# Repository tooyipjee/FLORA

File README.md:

FLORA: The Smart Garden Weather Station and Soil Moisture Monitor

In 2022, Europe faced its worst drought in over four decades. This marked a significant turning point for sustainable gardening practices across the continent. Amidst this crisis, there is an emerging solution that empowers communities to be more resilient and adaptive to extreme climates: FLORA - A Smart Garden Weather Station with Soil Moisture Monitoring.

The Need for Water-Efficient Practices in Europe's Gardens, Allotments, and Small Farms

The current climate crisis has made it imperative to rethink our approach towards water management and conservation. With the recent drought conditions across Europe, there is an urgent need to implement sustainable practices that can ensure a reliable food supply while conserving precious resources. The project at hand seeks to address this by creating smarter gardens and farms that are efficient in their use of water, thereby mitigating the risks associated with climate change-induced adversities.

Introducing FLORA: A Proof of Concept for Sustainable Gardening

FLORA is an innovative prototyping platform designed to enhance garden and farm productivity while promoting water conservation and sustainability. Built around a low-cost ESP32 SoC, it supports WiFi, BLE, and LoRa connectivity for efficient communication with other smart devices on the same network frequency band up to 3 km away.
e

The platform includes an ambient sensor and various inputs for integrating soil moisture sensors, providing a comprehensive view of environmental factors that influence plant growth. The goal is not just about making gardens more efficient; it's also about bringing communities back in control of their food production systems by making gardening processes rewarding and as effortless as possible.

What Makes FLORA Unique?

Long Range Communication: With the LoRa module, FLORA offers long-range communication up to approximately 2 miles/3 km. This feature is particularly beneficial for expansive gardens or allotments that require monitoring over larger areas without compromising on connectivity.

Soil Moisture Sensor Integration: The companion soil moisture sensor, based on capacitive sensing technology and insulated to prevent corrosion, provides real-time data about the water content in the top layer of the soil. This information is essential for optimizing irrigation practices and avoiding unnecessary water wastage.

Solar Power: FLORA runs on a solar panel powered by coin cell batteries, ensuring it operates sustainably without relying on conventional energy sources.

Vinduino Project Inspiration

The inspiration behind the design of FLORA comes from Reinier van der Lee's project, Vinduino, which showcases how simple electronics sensors can significantly reduce water usage in agriculture by up to 25%. The underlying principles and technologies have been adapted for use in gardening applications.

Building on Plant-Bot Project Experience

Reinier's experience with the Plant-Bot project laid a solid foundation for designing FLORA, allowing it to evolve into an outdoor-focused system that caters specifically to multiple plants and gardens.

Key Features of FLORA:

Compatibility with WiFi, BLE, and LoRa connectivity for seamless communication

Temperature accuracy within 0.3°C and humidity accuracy up to 3% RH using the SHT20 sensor

Capable of integrating various soil moisture sensors with capacitive-based technology

Long-range communication capabilities, extending FLORA's coverage area significantly

Efficient energy consumption powered by a solar panel and coin cell battery system

User-friendly design that empowers gardeners to take control of their plant care processes

Versatility in customization and integration with other smart devices within the same network frequency band

Specification Details:

Microcontroller: ESP32-WROOM-32E

WiFi Support: 802.11b/g/n standard

Bluetooth Capabilities: BLE 4.2 version

Flash Memory: 8MB capacity for firmware storage and execution

Programming Interface: USB over UART (CP2102) for direct programming and control

Environment Sensor: Incorporates the SHT20 sensor to measure temperature and humidity accurately

Soil Moisture Measurement: Utilizes capacitive sensing technology for reliable soil moisture readings

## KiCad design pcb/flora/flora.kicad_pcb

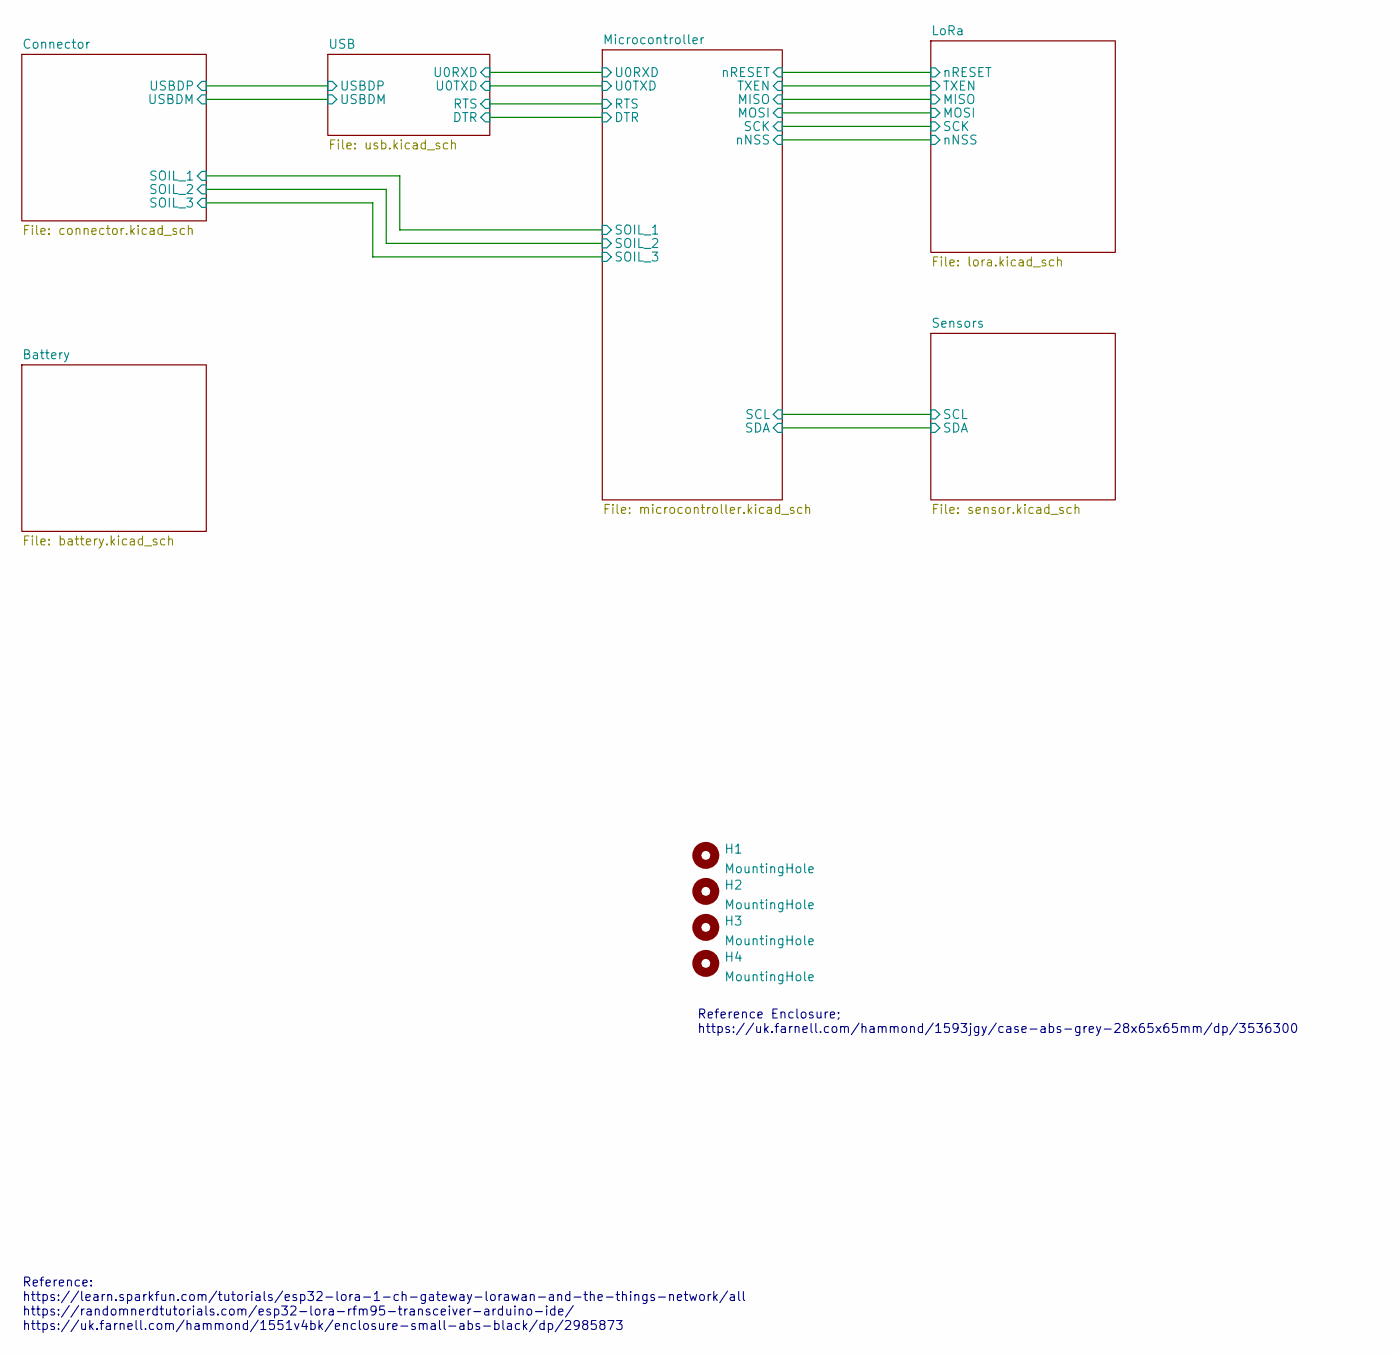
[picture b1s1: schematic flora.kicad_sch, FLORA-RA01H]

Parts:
H1, H2, H3, H4: MountingHole; MountingHole_3.2mm_M3_Small

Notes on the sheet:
Reference Enclosure; https://uk.farnell.com/hammond/1593jgy/case-abs-grey-28x65x65mm/dp/3536300
Reference: https://learn.sparkfun.com/tutorials/esp32-lora-1-ch-gateway-lorawan-and-the-things-network/all https://randomnerdtutorials.com/esp32-lora-rfm95-transceiver-arduino-ide/ https://uk.farnell.com/hammond/1551v4bk/enclosure-small-abs-black/dp/2985873

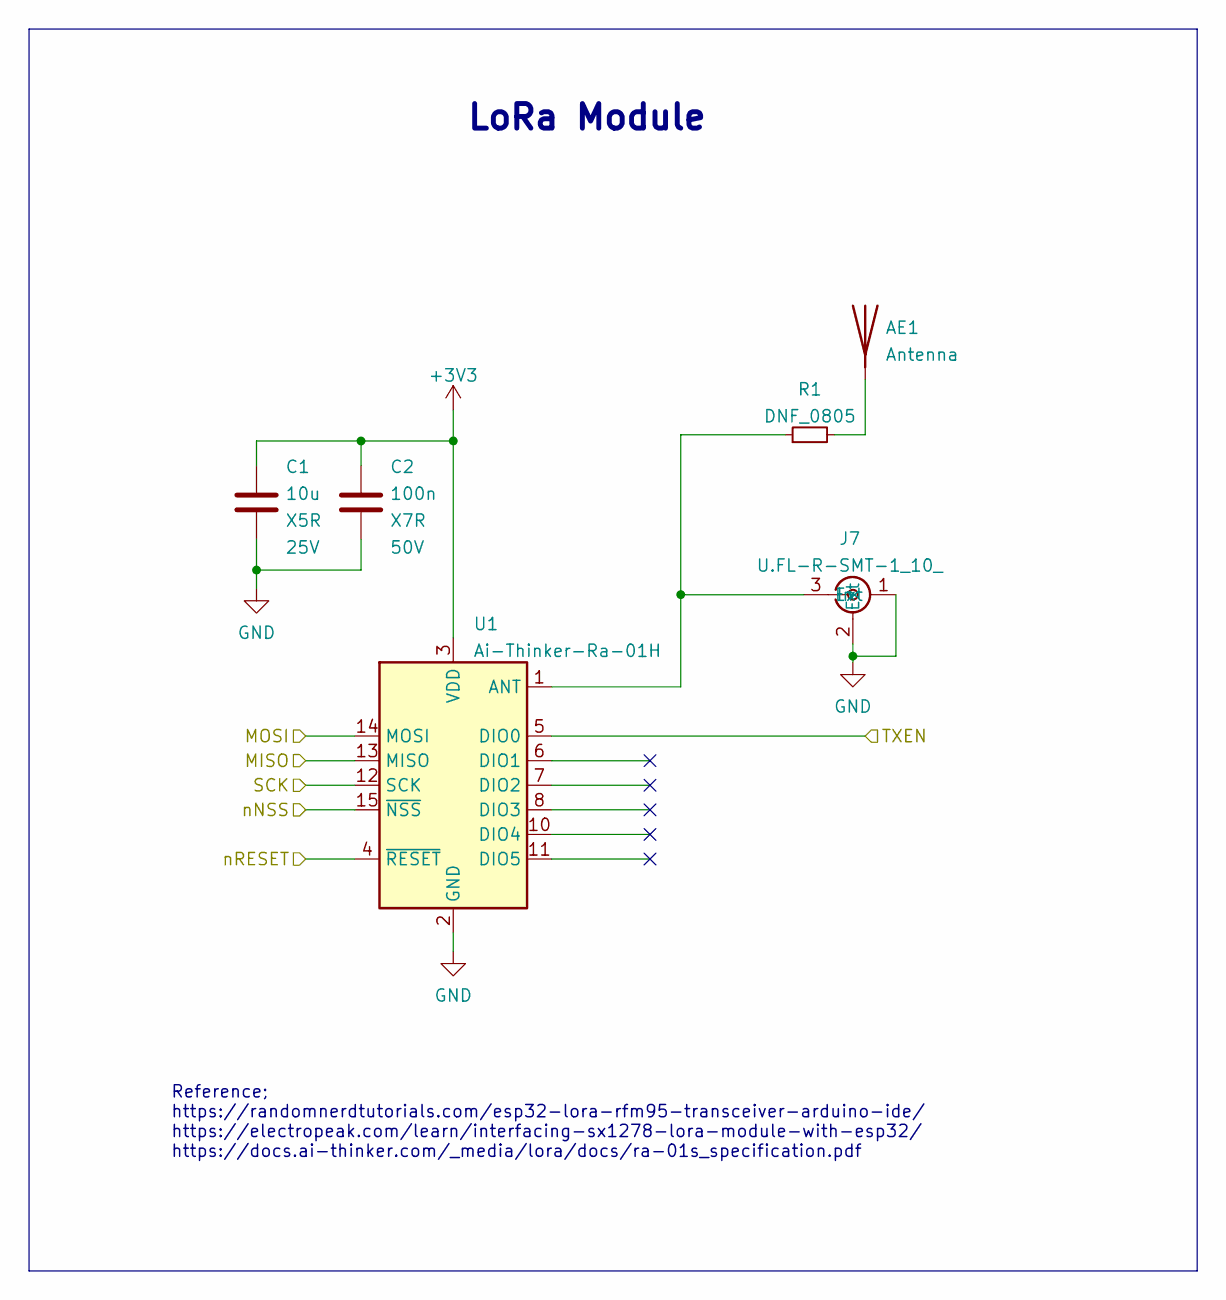
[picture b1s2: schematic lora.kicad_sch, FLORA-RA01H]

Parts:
AE1: Antenna; Texas_SWRA416_868MHz_915MHz
C1: 10u; C_0805_2012Metric; Voltage 25V; LCSC C15850
C2: 100n; C_0402_1005Metric; Voltage 50V; LCSC C307331
J7: U.FL-R-SMT-1_10_; Manufacturer_Part_Number U.FL-R-SMT-1(10); Mouser Part Number 798-U.FL-R-SMT-110
R1: DNF_0805; R_0805_2012Metric_Pad1.20x1.40mm_HandSolder
U1: Ai-Thinker-Ra-01H; Ai-Thinker-Ra-01-LoRa; LCSC C503593

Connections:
+3V3: C1.1, C2.1, U1.3 (VDD); also elsewhere on the board
GND: C1.2, C2.2, J7.1 (Ext), J7.2 (Ext), U1.2 (GND), U1.9 (GND), U1.16 (GND); also elsewhere on the board
GPIO2: U1.5 (DIO0); also elsewhere on the board
GPIO5: U1.15 (~NSS); also elsewhere on the board
GPIO14: U1.4 (~RESET); also elsewhere on the board
GPIO18: U1.12 (SCK); also elsewhere on the board
GPIO19: U1.13 (MISO); also elsewhere on the board
GPIO23: U1.14 (MOSI); also elsewhere on the board
unnamed: AE1.1 (A), R1.2
unnamed: J7.3 (In), R1.1, U1.1 (ANT)

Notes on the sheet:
LoRa Module
Reference; https://randomnerdtutorials.com/esp32-lora-rfm95-transceiver-arduino-ide/ https://electropeak.com/learn/interfacing-sx1278-lora-module-with-esp32/ https://docs.ai-thinker.com/_media/lora/docs/ra-01s_specification.pdf

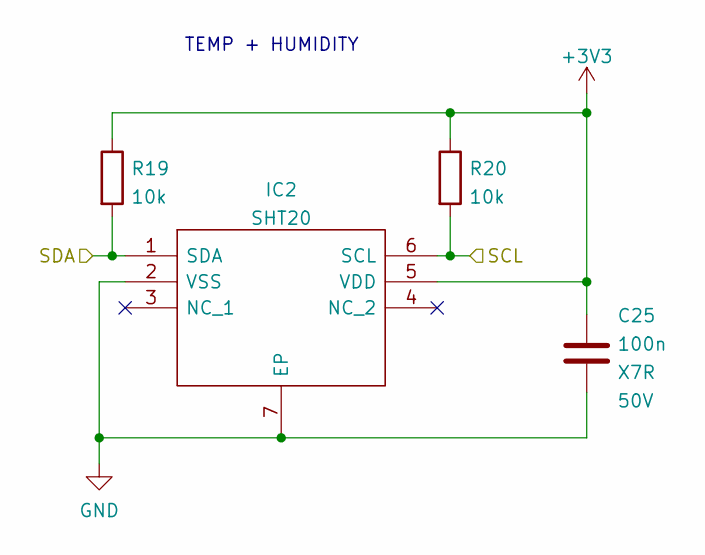
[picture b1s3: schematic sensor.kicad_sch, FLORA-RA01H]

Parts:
C25: 100n; C_0402_1005Metric; Voltage 50V; LCSC C307331
IC2: SHT20; SON100P300X300X110-7N; Mouser Part Number 403-SHT20
R19, R20: 10k; R_0402_1005Metric; LCSC C25744

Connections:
+3V3: C25.1, IC2.5 (VDD), R19.1, R20.1; also elsewhere on the board
GND: C25.2, IC2.2 (VSS), IC2.7 (EP); also elsewhere on the board
GPIO16: IC2.1 (SDA), R19.2; also elsewhere on the board
GPIO17: IC2.6 (SCL), R20.2; also elsewhere on the board

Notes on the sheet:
TEMP + HUMIDITY

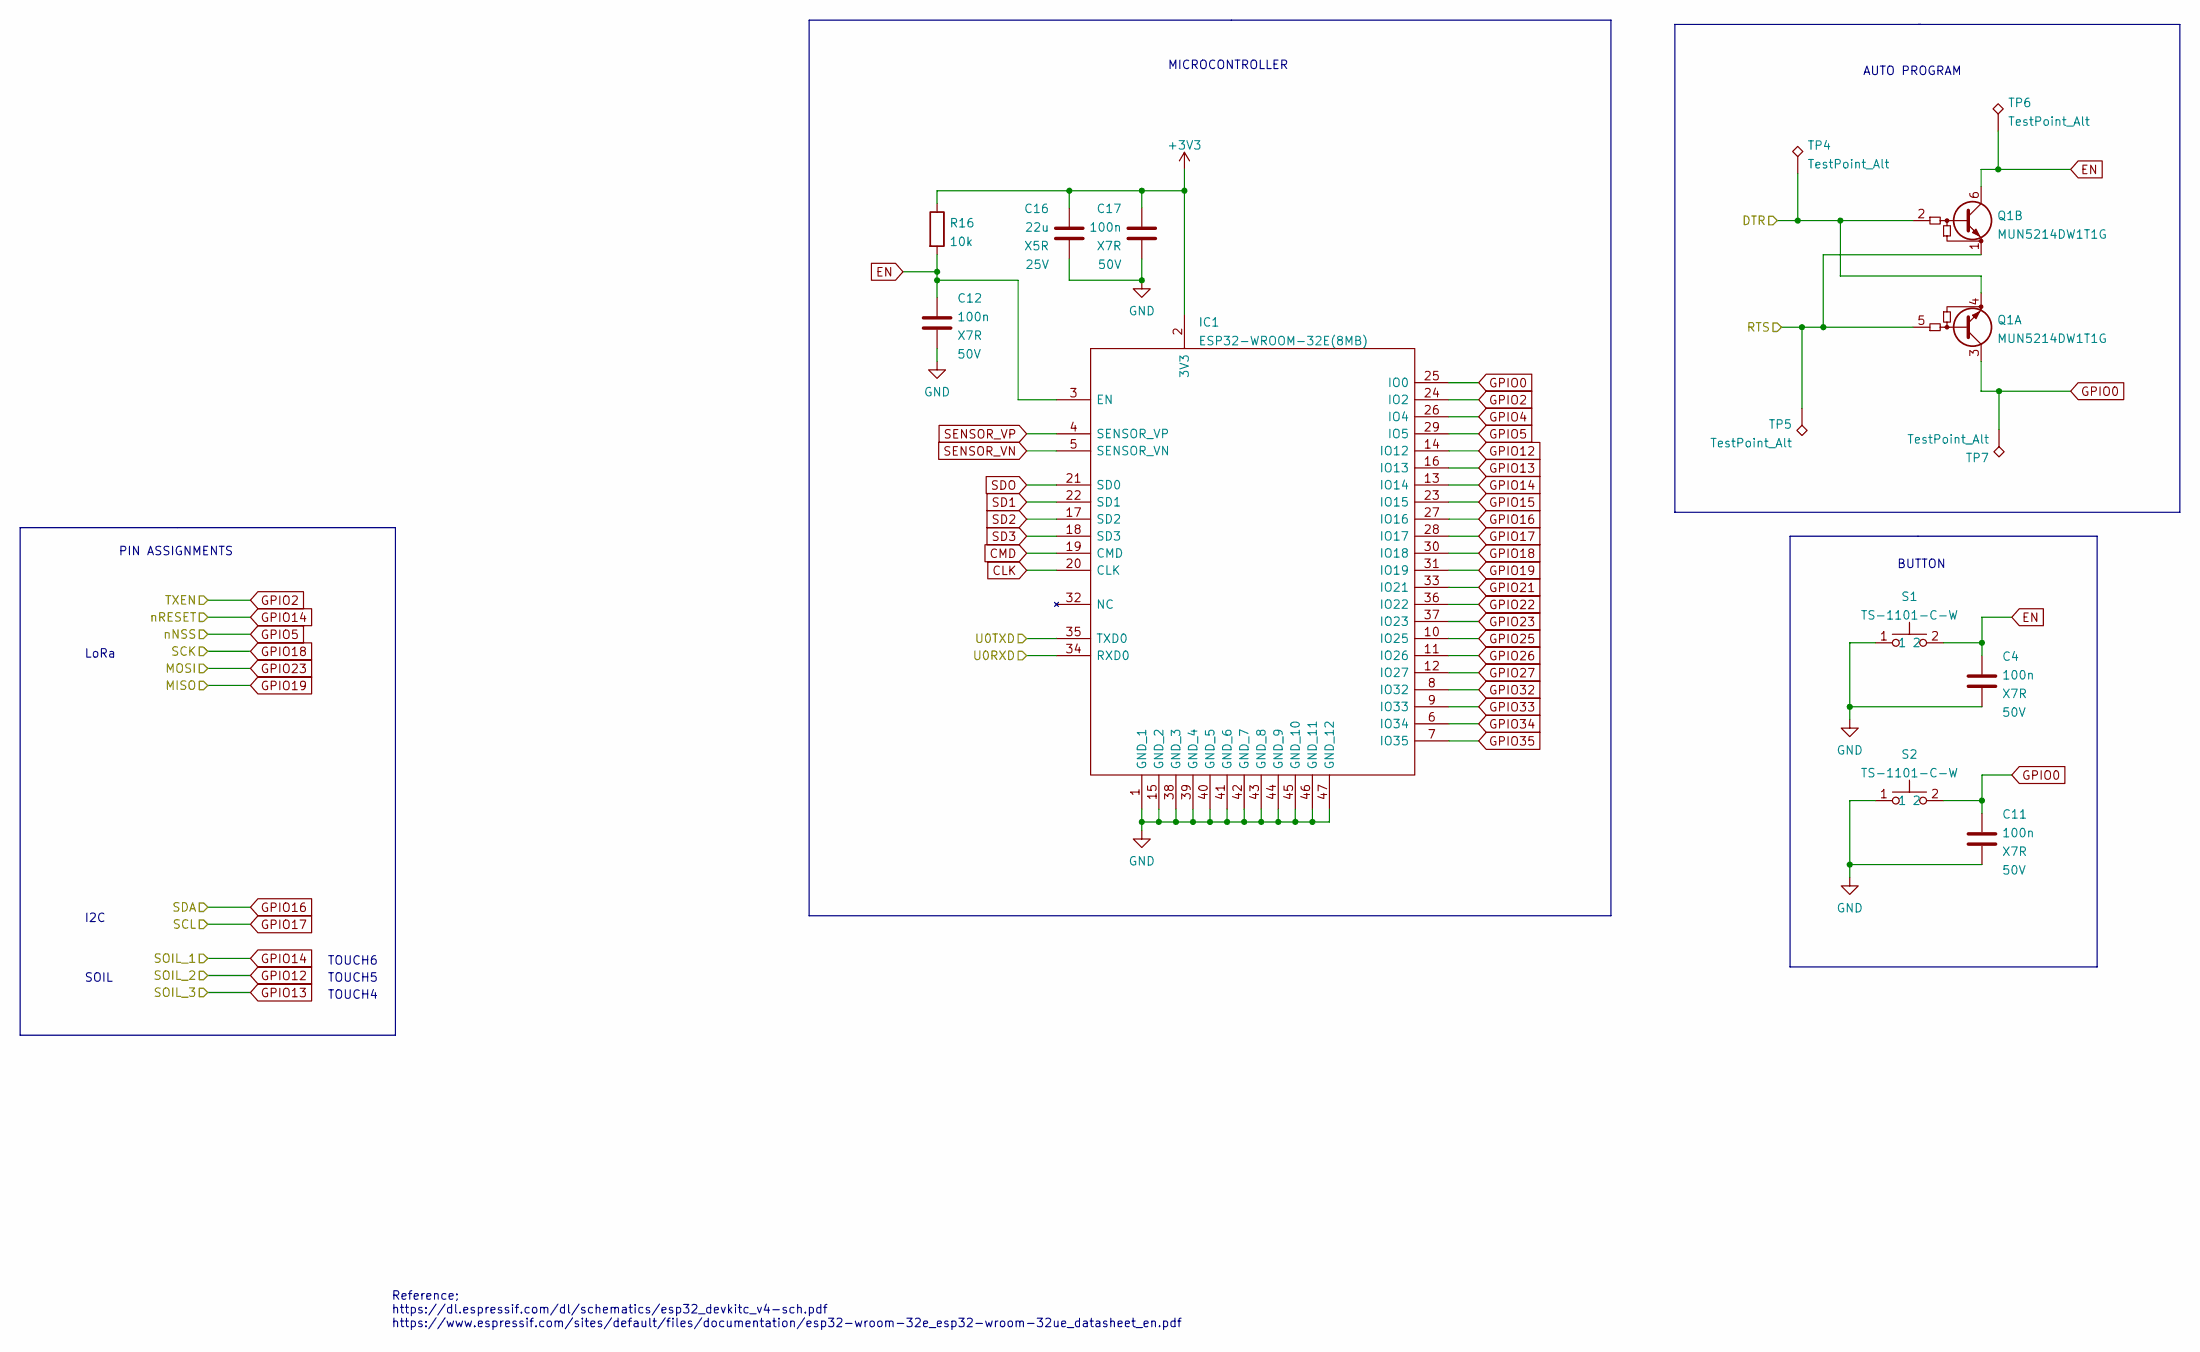
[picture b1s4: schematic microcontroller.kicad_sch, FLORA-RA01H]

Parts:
C4, C11, C12, C17: 100n; C_0402_1005Metric; Voltage 50V; LCSC C307331
C16: 22u; C_0805_2012Metric; Voltage 25V; LCSC C602037
IC1: ESP32-WROOM-32E(8MB); ESP32WROOM32E8MB; Manufacturer_Part_Number ESP32-WROOM-32E (8MB); Mouser Part Number 356-ESP32WRM32E164PH
Q1: MUN5214DW1T1G; SOT-363_SC-70-6; LCSC C94403
R16: 10k; R_0402_1005Metric; LCSC C25744
S1, S2: TS-1101-C-W; TS1101CW; Manufacturer_Part_Number TS-1101-C-W; LCSC C318938
TP4, TP5, TP6, TP7: TestPoint_Alt; TestPoint_Pad_1.0x1.0mm

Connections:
+3V3: C16.1, C17.1, IC1.2 (3V3), R16.1; also elsewhere on the board
/Microcontroller/DTR: Q1.2 (B2), Q1.4 (E1), TP4.1; also elsewhere on the board
/Microcontroller/RTS: Q1.1 (E2), Q1.5 (B1), TP5.1; also elsewhere on the board
/Microcontroller/U0RXD: IC1.34 (RXD0); also elsewhere on the board
/Microcontroller/U0TXD: IC1.35 (TXD0); also elsewhere on the board
CLK: IC1.20 (CLK)
CMD: IC1.19 (CMD)
EN: C4.2, C12.1, IC1.3 (EN), Q1.6 (C2), R16.2, S1.2, TP6.1
GND: C4.1, C11.1, C12.2, C16.2, C17.2, IC1.1 (GND_1), IC1.15 (GND_2), IC1.38 (GND_3), IC1.39 (GND_4), IC1.40 (GND_5), IC1.41 (GND_6), IC1.42 (GND_7), IC1.43 (GND_8), IC1.44 (GND_9), IC1.45 (GND_10), IC1.46 (GND_11), IC1.47 (GND_12), S1.1, S2.1; also elsewhere on the board
GPIO0: C11.2, IC1.25 (IO0), Q1.3 (C1), S2.2, TP7.1
GPIO2: IC1.24 (IO2); also elsewhere on the board
GPIO4: IC1.26 (IO4)
GPIO5: IC1.29 (IO5); also elsewhere on the board
GPIO12: IC1.14 (IO12); also elsewhere on the board
GPIO13: IC1.16 (IO13); also elsewhere on the board
GPIO14: IC1.13 (IO14); also elsewhere on the board
GPIO15: IC1.23 (IO15)
GPIO16: IC1.27 (IO16); also elsewhere on the board
GPIO17: IC1.28 (IO17); also elsewhere on the board
GPIO18: IC1.30 (IO18); also elsewhere on the board
GPIO19: IC1.31 (IO19); also elsewhere on the board
GPIO21: IC1.33 (IO21)
GPIO22: IC1.36 (IO22)
GPIO23: IC1.37 (IO23); also elsewhere on the board
GPIO25: IC1.10 (IO25)
GPIO26: IC1.11 (IO26)
GPIO27: IC1.12 (IO27)
GPIO32: IC1.8 (IO32)
GPIO33: IC1.9 (IO33)
GPIO34: IC1.6 (IO34)
GPIO35: IC1.7 (IO35)
SD1: IC1.22 (SD1)
SD2: IC1.17 (SD2)
SD3: IC1.18 (SD3)
SDO: IC1.21 (SD0)
SENSOR_VN: IC1.5 (SENSOR_VN)
SENSOR_VP: IC1.4 (SENSOR_VP)

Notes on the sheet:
AUTO PROGRAM
PIN ASSIGNMENTS
BUTTON
MICROCONTROLLER
SOIL
Reference; https://dl.espressif.com/dl/schematics/esp32_devkitc_v4-sch.pdf https://www.espressif.com/sites/default/files/documentation/esp32-wroom-32e_esp32-wroom-32ue_datasheet_en.pdf
LoRa
TOUCH6
TOUCH4
I2C
TOUCH5

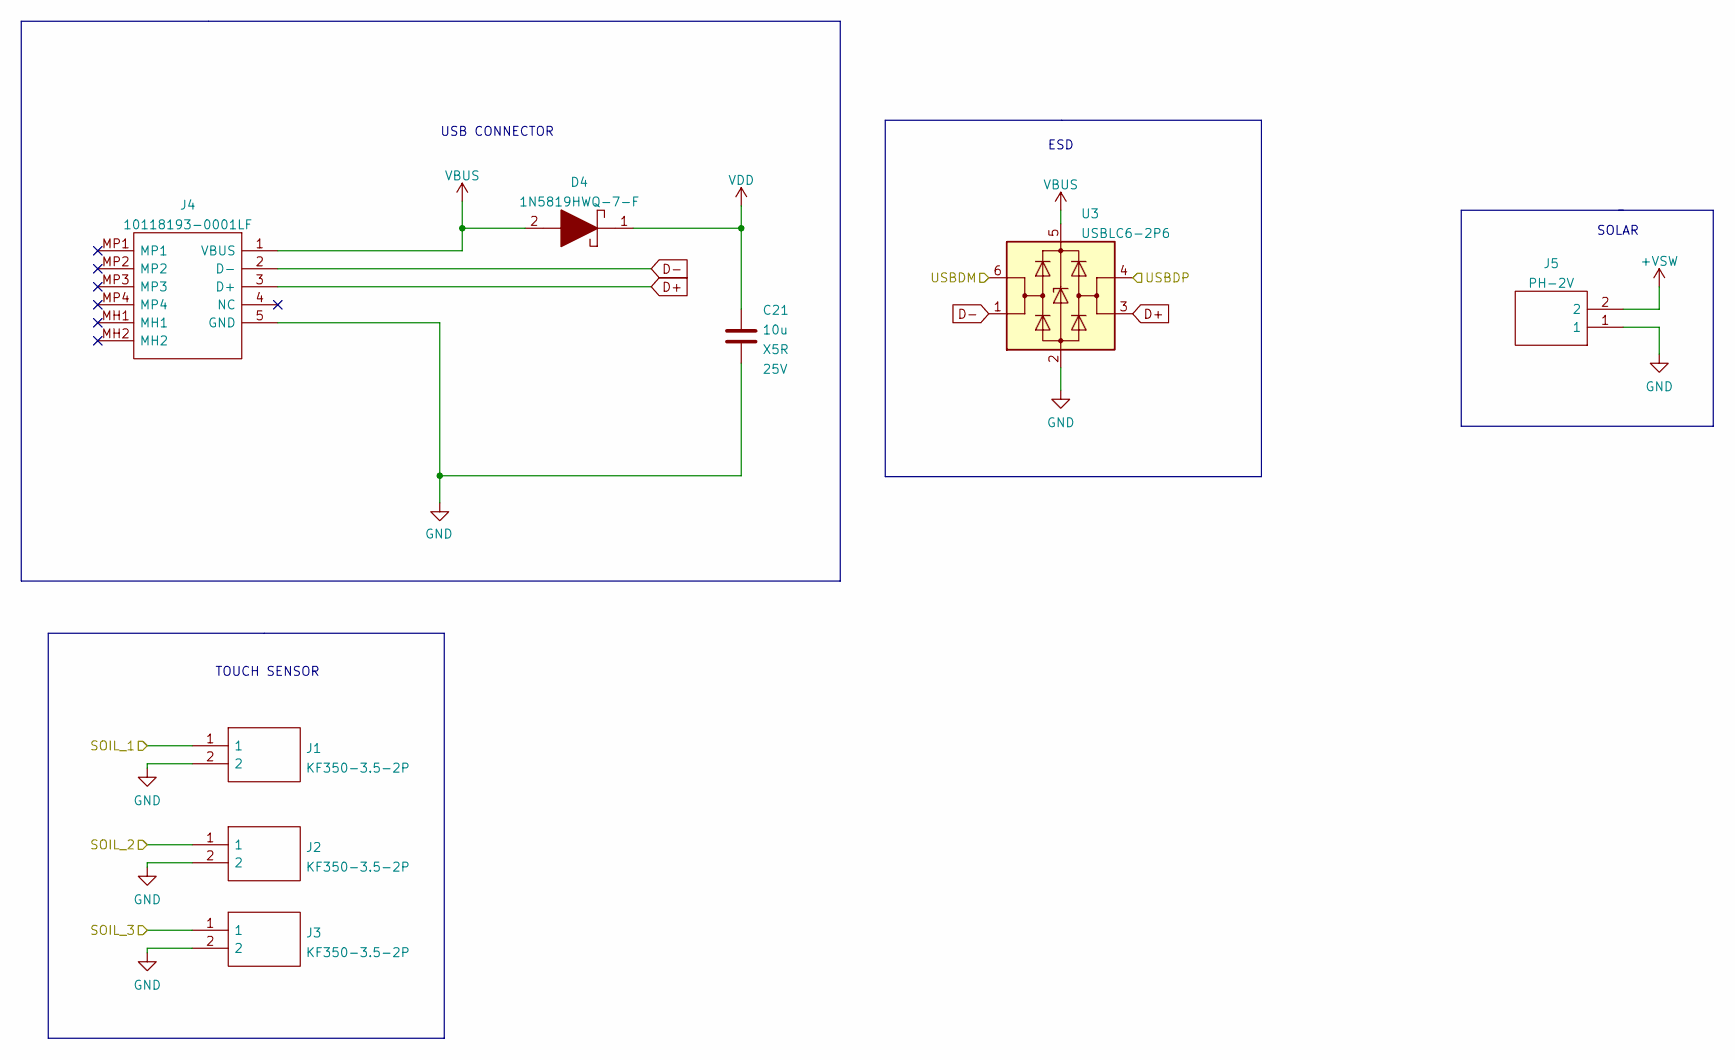
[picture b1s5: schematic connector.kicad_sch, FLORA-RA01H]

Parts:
C21: 10u; C_0805_2012Metric; Voltage 25V; LCSC C15850
D4: 1N5819HWQ-7-F; SOD3716X145N; Manufacturer_Part_Number 1N5819HWQ-7-F; Mouser Part Number 621-1N5819HWQ-7-F
J1, J2, J3: KF350-3.5-2P; KF350352P; Manufacturer_Part_Number KF350-3.5-2P; LCSC C474892
J4: 10118193-0001LF; 101181930001LF; Manufacturer_Part_Number 10118193-0001LF; Mouser Part Number 649-10118193-0001LF
J5: PH-2V; SHDR2W52P0X200_1X2_600X460X630P; Manufacturer_Part_Number PH-2AK; LCSC C146082
U3: USBLC6-2P6; SOT-666; LCSC C2827693

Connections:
+VSW: J5.2; also elsewhere on the board
/Connector/USBDM: U3.6 (I/O1); also elsewhere on the board
/Connector/USBDP: U3.4 (I/O2); also elsewhere on the board
D+: J4.3 (D+), U3.3 (I/O2)
D-: J4.2 (D-), U3.1 (I/O1)
GND: C21.2, J1.2, J2.2, J3.2, J4.5 (GND), J5.1, U3.2 (GND); also elsewhere on the board
GPIO12: J2.1; also elsewhere on the board
GPIO13: J3.1; also elsewhere on the board
GPIO14: J1.1; also elsewhere on the board
VBUS: D4.2, J4.1 (VBUS), U3.5 (VBUS)
VDD: C21.1, D4.1; also elsewhere on the board

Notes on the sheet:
SOLAR
USB CONNECTOR
ESD
TOUCH SENSOR

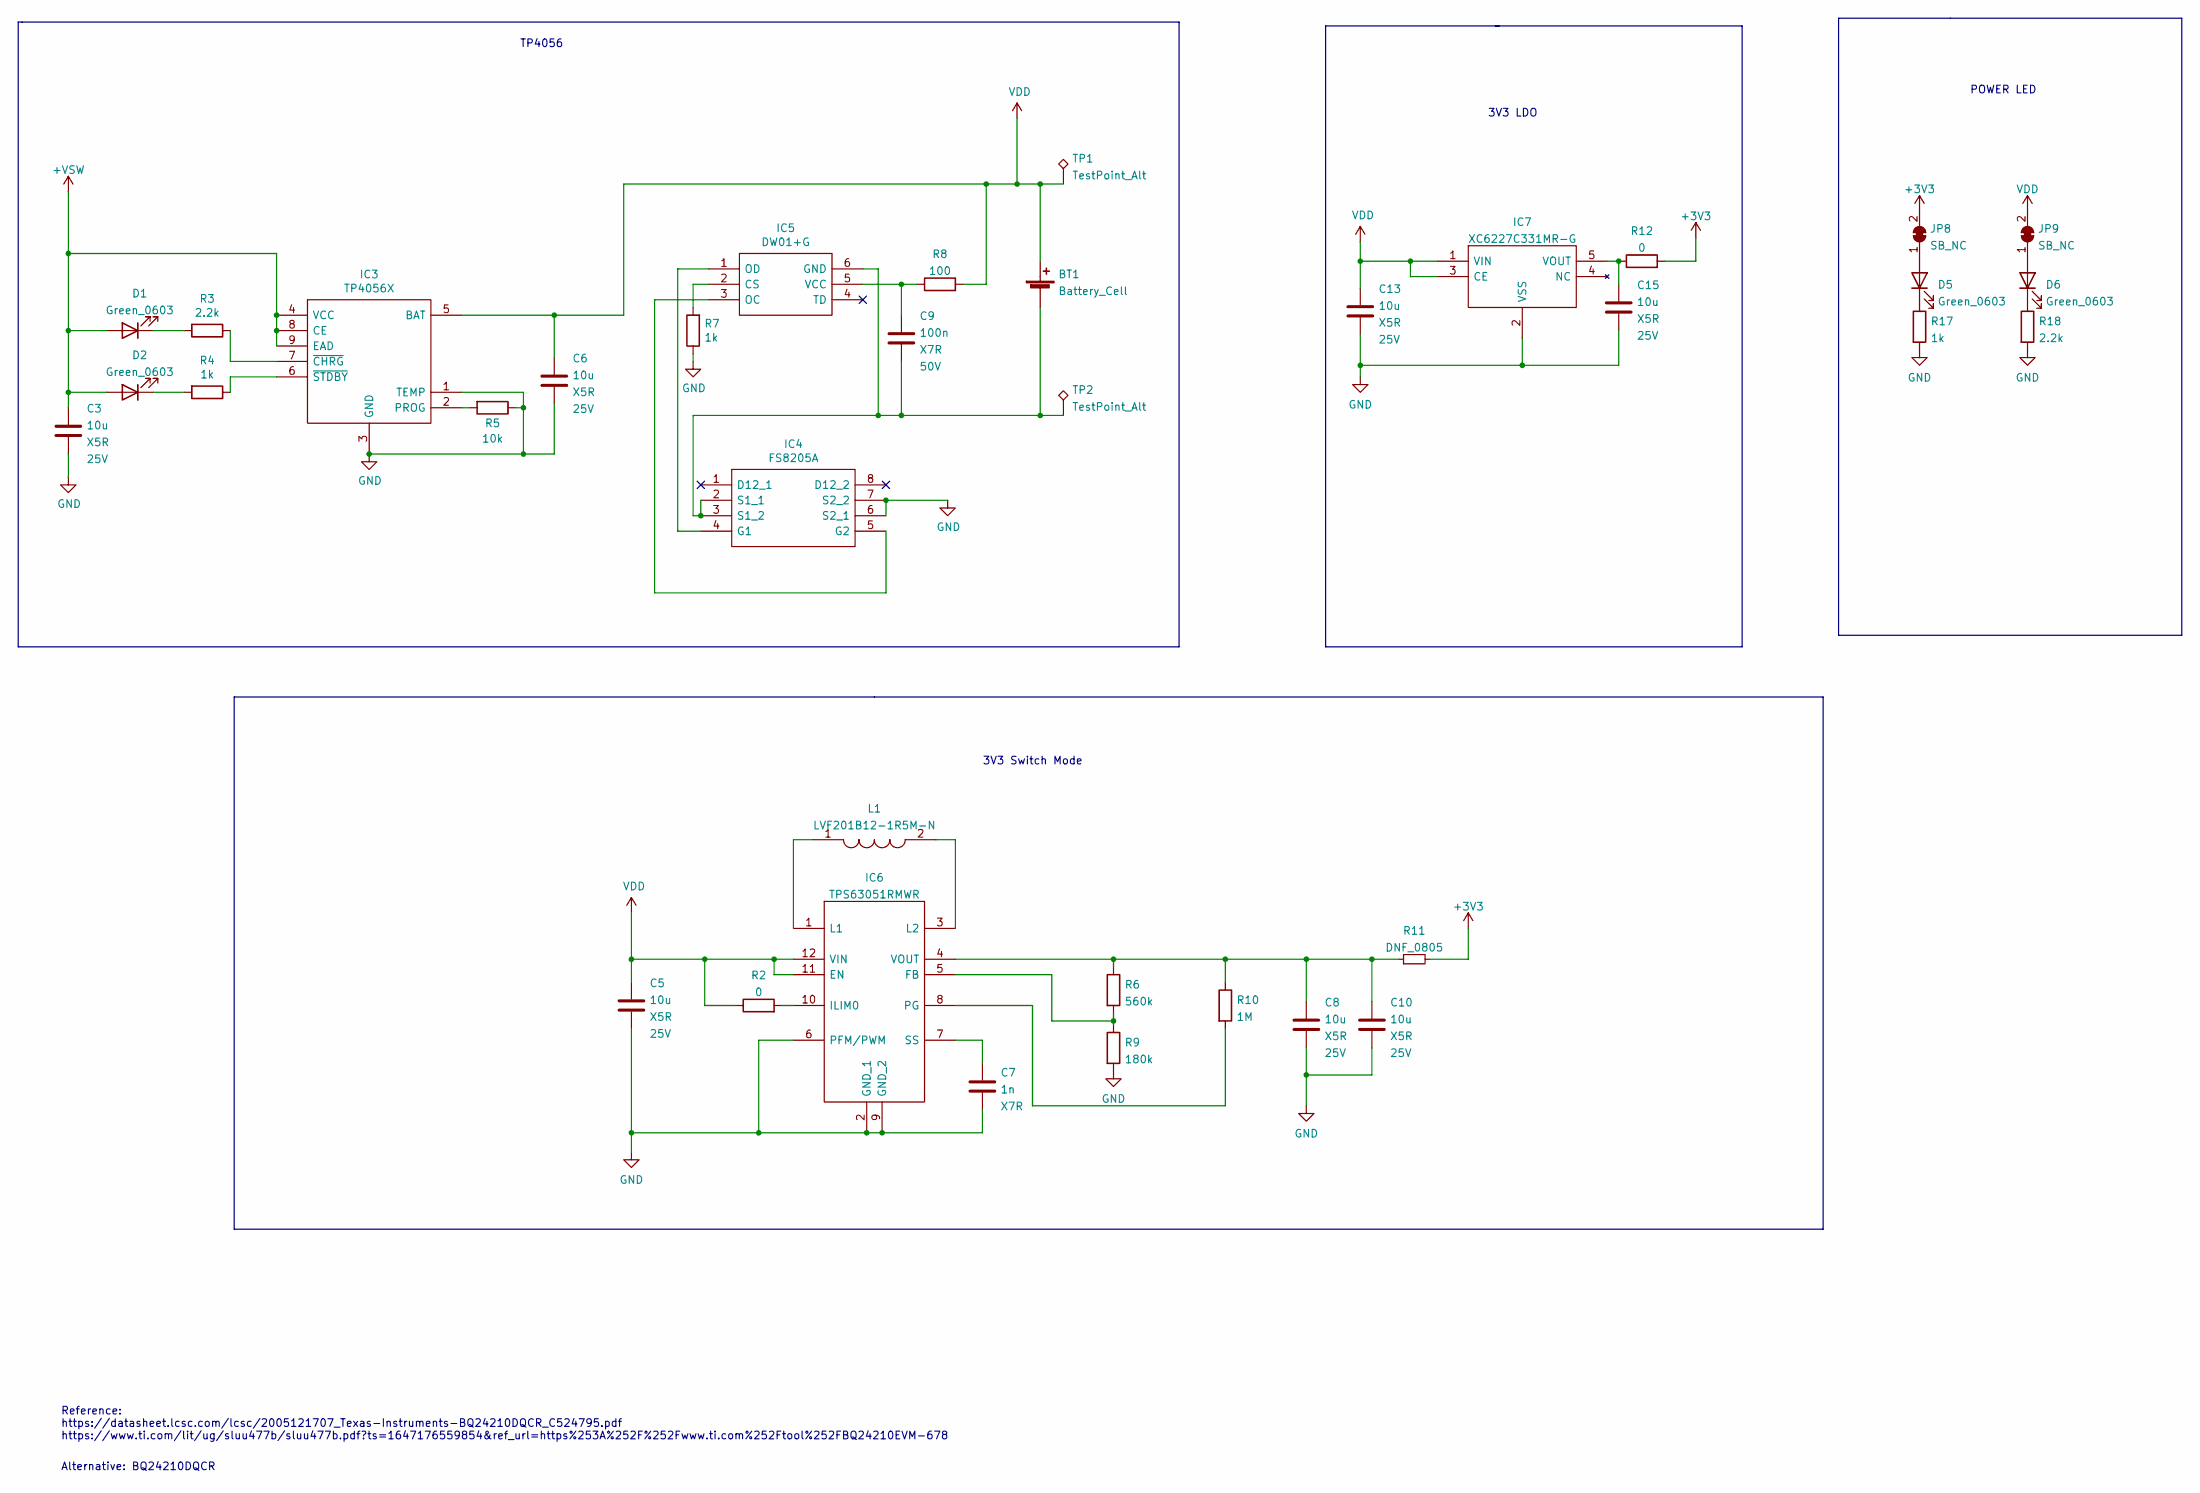
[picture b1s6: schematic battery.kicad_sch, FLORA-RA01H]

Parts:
BT1: Battery_Cell; BS-24-B4AK014
C3, C5, C6, C8, C10, C13, C15: 10u; C_0805_2012Metric; Voltage 25V; LCSC C15850
C7: 1n; C_0402_1005Metric; LCSC C1523
C9: 100n; C_0402_1005Metric; Voltage 50V; LCSC C307331
D1, D2, D5, D6: Green_0603; LED_0603_1608Metric; LCSC C72043
IC3: TP4056X; SOIC127P600X175-9N; Manufacturer_Part_Number TP4056X; LCSC C16581
IC4: FS8205A; SOP65P640X120-8N; Manufacturer_Part_Number FS8205A; LCSC C16052
IC5: DW01+G; SOT95P280X145-6N; Manufacturer_Part_Number DW01+G; LCSC C14213
IC6: TPS63051RMWR; QFN50P250X250X100-12N-D; Manufacturer_Part_Number TPS63051RMWR; Mouser Part Number 595-TPS63051RMWR
IC7: XC6227C331MR-G; SOT95P280X130-5N; Manufacturer_Part_Number XC6227C331MR-G; Mouser Part Number 865-XC6227C331MR-G
JP8, JP9: SB_NC; SolderJumper-2_P1.3mm_Bridged_Pad1.0x1.5mm
L1: LVF201B12-1R5M-N; LVF201B121R5MN; Manufacturer_Part_Number LVF201B12-1R5M-N; LCSC C329583
R2, R12: 0; R_0805_2012Metric_Pad1.20x1.40mm_HandSolder; LCSC C17477
R3, R18: 2.2k; R_0402_1005Metric; LCSC C25879
R4, R7, R17: 1k; R_0402_1005Metric; LCSC C11702
R5: 10k; R_0402_1005Metric; LCSC C25744
R6: 560k; R_0603_1608Metric; LCSC C23203
R8: 100; R_0402_1005Metric; LCSC C25076
R9: 180k; R_0402_1005Metric; LCSC C138046
R10: 1M; R_0402_1005Metric; LCSC C26083
R11: DNF_0805; R_0805_2012Metric_Pad1.20x1.40mm_HandSolder
TP1, TP2: TestPoint_Alt; TestPoint_Pad_1.0x1.0mm

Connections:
+3V3: JP8.2 (B), R11.2, R12.2; also elsewhere on the board
+VSW: C3.1, D1.2 (A), D2.2 (A), IC3.4 (VCC), IC3.8 (CE), IC3.9 (EAD); also elsewhere on the board
GND: C3.2, C5.2, C6.2, C7.2, C8.2, C10.2, C13.2, C15.2, IC3.1 (TEMP), IC3.3 (GND), IC4.6 (S2_1), IC4.7 (S2_2), IC6.2 (GND_1), IC6.6 (PFM/PWM), IC6.9 (GND_2), IC7.2 (VSS), R5.1, R7.1, R9.2, R17.2, R18.2; also elsewhere on the board
unnamed: BT1.2 (-), C9.2, IC4.2 (S1_1), IC4.3 (S1_2), IC5.6 (GND), TP2.1
unnamed: C7.1, IC6.7 (SS)
unnamed: C8.1, C10.1, IC6.4 (VOUT), R6.1, R10.1, R11.1
unnamed: C9.1, IC5.5 (VCC), R8.1
unnamed: D1.1 (K), R3.2
unnamed: D2.1 (K), R4.2
unnamed: D5.1 (K), R17.1
unnamed: D5.2 (A), JP8.1 (A)
unnamed: D6.1 (K), R18.1
unnamed: D6.2 (A), JP9.1 (A)
unnamed: IC3.2 (PROG), R5.2
unnamed: IC3.6 (~STDBY), R4.1
unnamed: IC3.7 (~CHRG), R3.1
unnamed: IC4.4 (G1), IC5.1 (OD)
unnamed: IC4.5 (G2), IC5.3 (OC)
unnamed: IC5.2 (CS), R7.2
unnamed: IC6.1 (L1), L1.1
unnamed: IC6.3 (L2), L1.2
unnamed: IC6.5 (FB), R6.2, R9.1
unnamed: IC6.8 (PG), R10.2
unnamed: IC6.10 (ILIM0), R2.2
unnamed 58: C15.1, IC7.5 (VOUT), R12.1; also elsewhere on the board
VDD: BT1.1 (+), C5.1, C6.1, C13.1, IC3.5 (BAT), IC6.11 (EN), IC6.12 (VIN), IC7.1 (VIN), IC7.3 (CE), JP9.2 (B), R2.1, R8.2, TP1.1; also elsewhere on the board

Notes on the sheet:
3V3 Switch Mode
Reference: https://datasheet.lcsc.com/lcsc/2005121707_Texas-Instruments-BQ24210DQCR_C524795.pdf https://www.ti.com/lit/ug/sluu477b/sluu477b.pdf?ts=1647176559854&ref_url=https%253A%252F%252Fwww.ti.com%252Ftool%252FBQ24210EVM-678
POWER LED
TP4056
Alternative: BQ24210DQCR
3V3 LDO

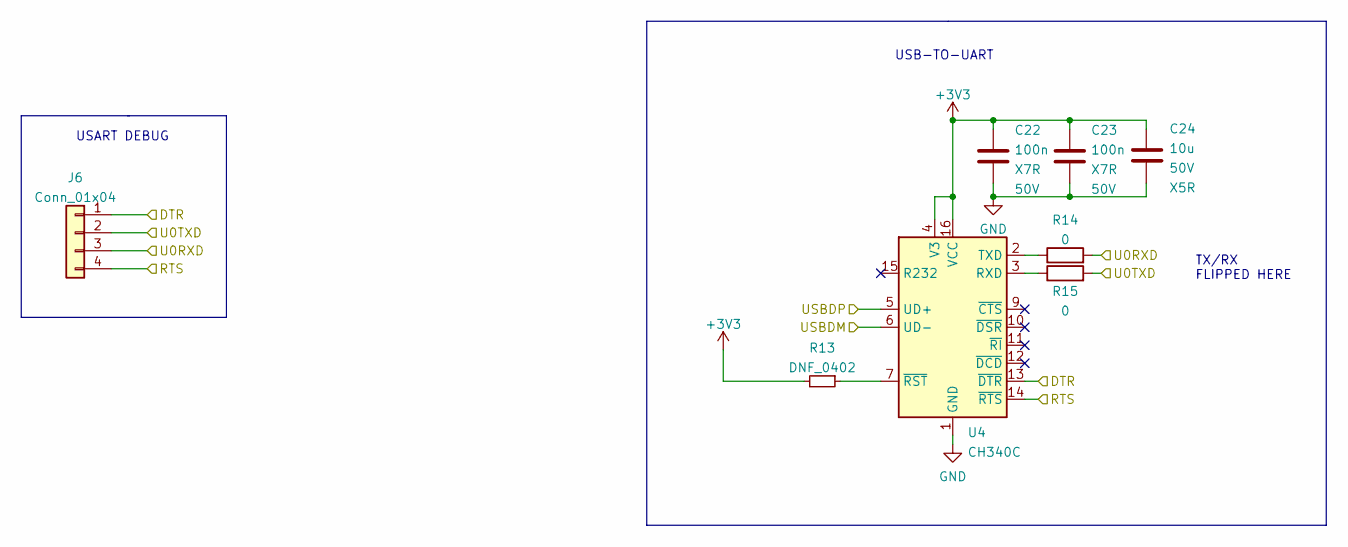
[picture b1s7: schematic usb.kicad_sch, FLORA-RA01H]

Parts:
C22, C23: 100n; C_0402_1005Metric; Voltage 50V; LCSC C307331
C24: 10u; C_0805_2012Metric; Rated Voltage 50V; LCSC C440198
J6: Conn_01x04; PinHeader_1x04_P1.27mm_Vertical
R13: DNF_0402; R_0402_1005Metric
R14, R15: 0; R_0805_2012Metric_Pad1.20x1.40mm_HandSolder; LCSC C17477
U4: CH340C; SOIC-16_3.9x9.9mm_P1.27mm; LCSC C84681

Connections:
+3V3: C22.1, C23.1, C24.1, R13.2, U4.4 (V3), U4.16 (VCC); also elsewhere on the board
/Connector/USBDM: U4.6 (UD-); also elsewhere on the board
/Connector/USBDP: U4.5 (UD+); also elsewhere on the board
/Microcontroller/DTR: J6.1, U4.13 (~DTR); also elsewhere on the board
/Microcontroller/RTS: J6.4, U4.14 (~RTS); also elsewhere on the board
/Microcontroller/U0RXD: J6.3, R14.2; also elsewhere on the board
/Microcontroller/U0TXD: J6.2, R15.2; also elsewhere on the board
GND: C22.2, C23.2, C24.2, U4.1 (GND); also elsewhere on the board
unnamed: R13.1, U4.7 (~RST)
unnamed: R14.1, U4.2 (TXD)
unnamed: R15.1, U4.3 (RXD)

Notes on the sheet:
USB-TO-UART
USART DEBUG
TX/RX FLIPPED HERE

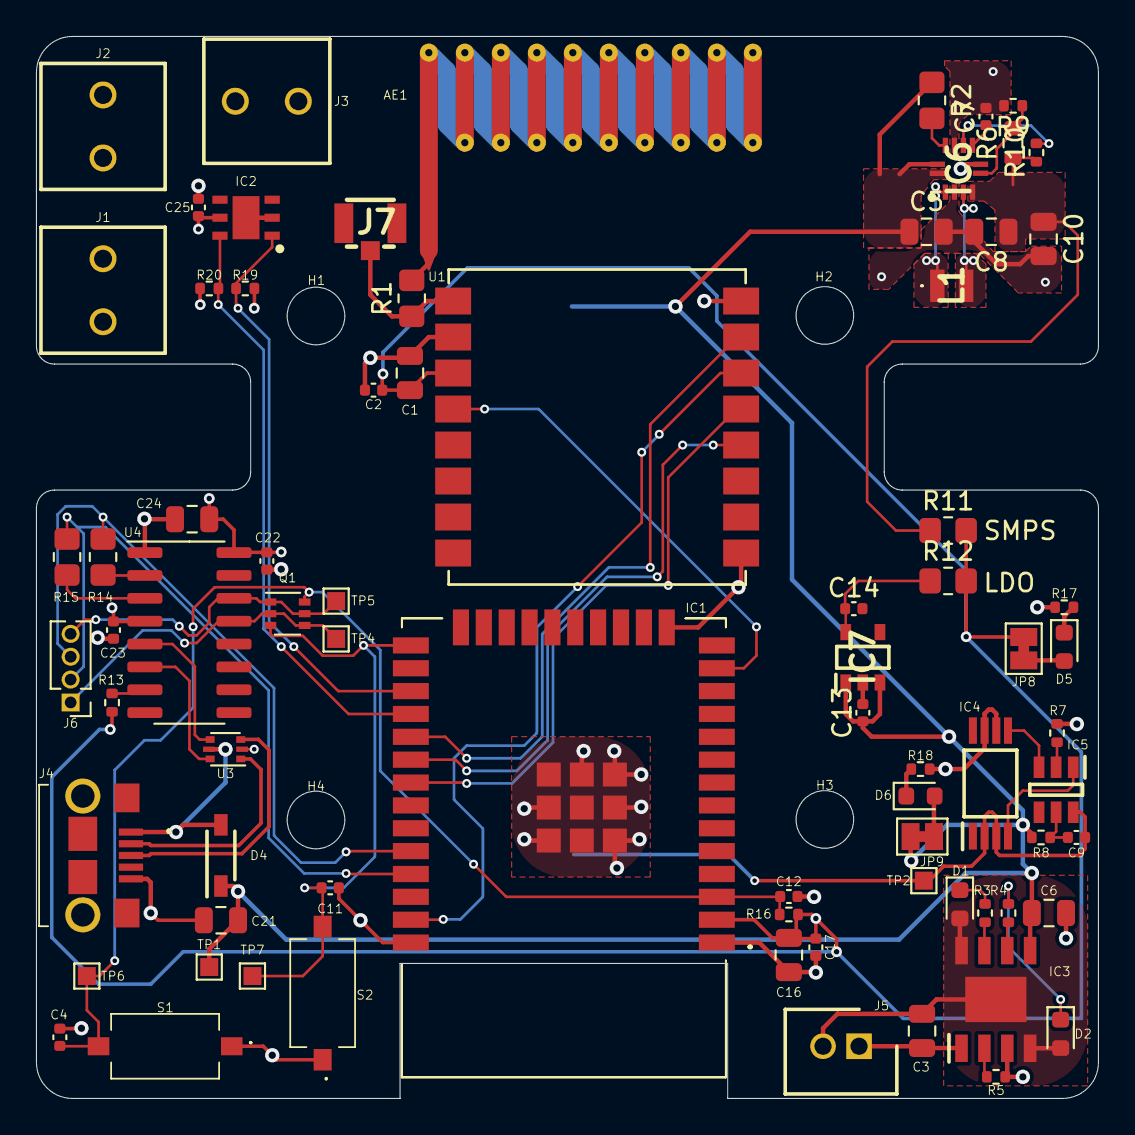
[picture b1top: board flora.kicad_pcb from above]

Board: 4 copper layers, 59.0 x 59.0 mm, 81 parts (1 on the bottom side), 52 nets.

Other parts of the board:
C14: 10u_0402; C_0402_1005Metric

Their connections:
GND: C14.2; also elsewhere on the board
unnamed 58: C14.1; also elsewhere on the board

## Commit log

2022-04-18 updated FLORA
2022-04-27 Added comments to power
2022-04-27 Removed header
2022-04-27 released Rev A
2022-06-05 added image
2022-06-05 photos
2022-07-01 commit backups
2022-07-01 Replaced SMPS
2022-12-03 Started new version using RFM95
2022-12-05 Finished schematic for RA-01 design
2022-12-05 replaced ra 01 with rfm95
2022-12-05 base placement completed
2023-02-20 finished smps layout
2023-04-07 new version of flora
